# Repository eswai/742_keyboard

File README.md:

# 742 KEYBOARD

742はOLED搭載、54キーの分割キーボードです。
ファームウェアは [QMK](https://github.com/eswai/qmk_firmware/tree/master/keyboards/eswai/742) を参照ください。

本キーボードはMITライセンスです。

foostan氏のKiCADライブラリ[kbd](https://github.com/foostan/kbd)を使用させていただきました。

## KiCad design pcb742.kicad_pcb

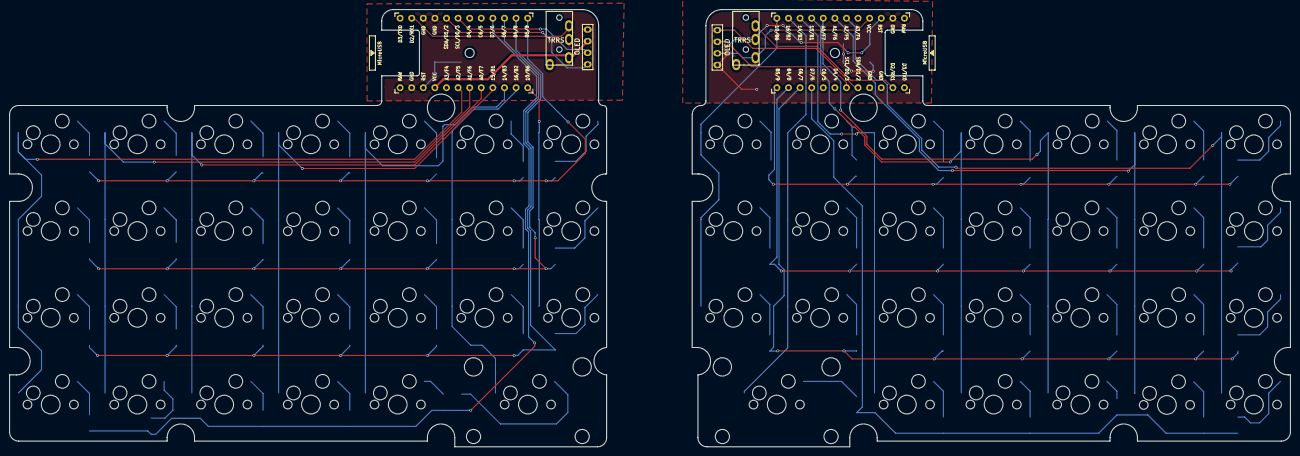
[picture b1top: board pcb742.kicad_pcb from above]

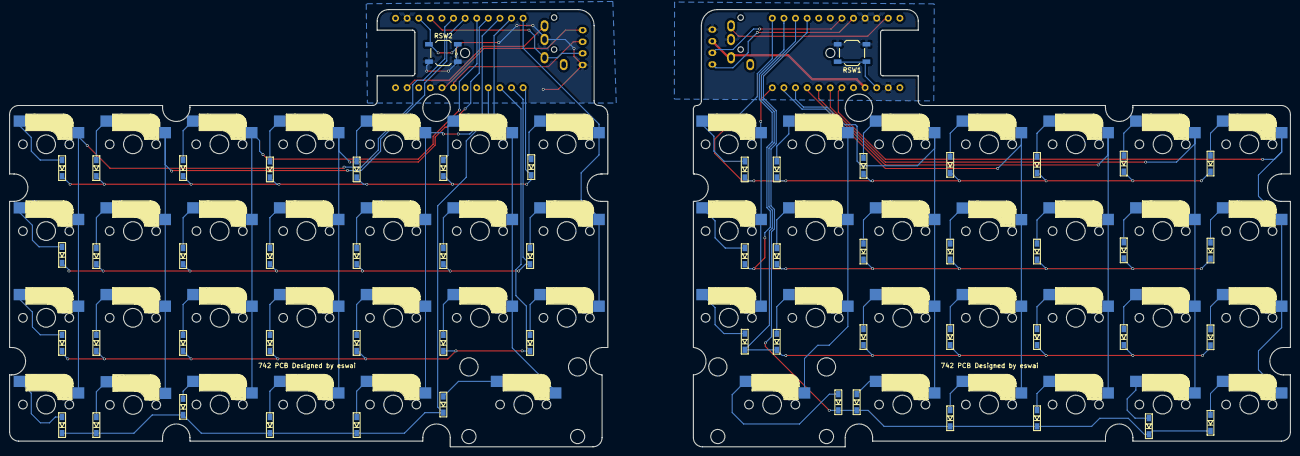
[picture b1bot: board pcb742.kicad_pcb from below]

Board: 2 copper layers, 280.5 x 95.8 mm, 116 parts (56 on the bottom side), 88 nets.

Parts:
D1, D2, D3, D4, D5, D6, D7, D8, D9, D10, D11, D12, D13, D14, D15, D16, D17, D18, D19, D20, D21, D22, D23, D24, D25, D26, D27, D28, D29, D30, D31, D32, D33, D34, D35, D36, D37, D38, D39, D40, D41, D42, D43, D44, D45, D46, D47, D48, D49, D50, D51, D52, D53, D54: D; D3_SMD_v2
J1, J3: MJ-4PP-9; MJ-4PP-9_1side
J2, J4: OLED; OLED_1side
RSW1, RSW2: SW_PUSH; SW_SPST_TL3342
SW1, SW2, SW3, SW4, SW5, SW6, SW7, SW8, SW9, SW10, SW11, SW12, SW13, SW14, SW15, SW16, SW17, SW18, SW19, SW20, SW21, SW22, SW23, SW24, SW25, SW26, SW27, SW28, SW29, SW30, SW31, SW32, SW33, SW34, SW35, SW36, SW37, SW38, SW39, SW40, SW41, SW42, SW43, SW44, SW45, SW46, SW47, SW48, SW49, SW50, SW51, SW52, SW53, SW54: SW_PUSH; CherryMX_Hotswap
U1, U2: ProMicro; ProMicro_v3

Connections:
GND: J1.C, J2.4, RSW1.2, U1.3, U1.4, U1.23
GNDA: J3.C, J4.4, RSW2.2, U2.3, U2.4, U2.23
unnamed: D1.2, SW1.2
unnamed: D2.2, SW2.2
unnamed: D3.2, SW3.2
unnamed: D4.2, SW4.2
unnamed: D5.2, SW5.2
unnamed: D6.2, SW6.2
unnamed: D7.2, SW7.2
unnamed: D8.2, SW8.2
unnamed: D9.2, SW9.2
unnamed: D10.2, SW10.2
unnamed: D11.2, SW11.2
unnamed: D12.2, SW12.2
unnamed: D13.2, SW13.2
unnamed: D14.2, SW14.2
unnamed: D15.2, SW15.2
unnamed: D16.2, SW16.2
unnamed: D17.2, SW17.2
unnamed: D18.2, SW18.2
unnamed: D19.2, SW19.2
unnamed: D20.2, SW20.2
unnamed: D21.2, SW21.2
unnamed: D22.2, SW22.2
unnamed: D23.2, SW23.2
unnamed: D24.2, SW24.2
unnamed: D25.2, SW25.2
unnamed: D26.2, SW26.2
unnamed: D27.2, SW27.2
unnamed: D28.2, SW28.2
unnamed: D29.2, SW29.2
unnamed: D30.2, SW30.2
unnamed: D31.2, SW31.2
unnamed: D32.2, SW32.2
unnamed: D33.2, SW33.2
unnamed: D34.2, SW34.2
unnamed: D35.2, SW35.2
unnamed: D36.2, SW36.2
unnamed: D37.2, SW37.2
unnamed: D38.2, SW38.2
unnamed: D39.2, SW39.2
unnamed: D40.2, SW40.2
unnamed: D41.2, SW41.2
unnamed: D42.2, SW42.2
unnamed: D43.2, SW43.2
unnamed: D44.2, SW44.2
unnamed: D45.2, SW45.2
unnamed: D46.2, SW46.2
unnamed: D47.2, SW47.2
unnamed: D48.2, SW48.2
unnamed: D49.2, SW49.2
unnamed: D50.2, SW50.2
unnamed: D51.2, SW51.2
unnamed: D52.2, SW52.2
unnamed: D53.2, SW53.2
unnamed: D54.2, SW54.2
SCL: J2.2, U1.6
SCL_r: J4.2, U2.6
SDA: J2.1, U1.5
SDA_r: J4.1, U2.5
VCC: J1.D, J2.3, U1.21
VDD: J3.D, J4.3, U2.21
col0: SW1.1, SW8.1, SW15.1, SW22.1, U1.19
col0_r: SW28.1, SW35.1, SW42.1, SW49.1, U2.19
col1: SW2.1, SW9.1, SW16.1, SW23.1, U1.18
col1_r: SW29.1, SW36.1, SW43.1, SW50.1, U2.18
col2: SW3.1, SW10.1, SW17.1, SW24.1, U1.17
col2_r: SW30.1, SW37.1, SW44.1, SW51.1, U2.17
col3: SW4.1, SW11.1, SW18.1, SW25.1, U1.16
col3_r: SW31.1, SW38.1, SW45.1, SW52.1, U2.16
col4: SW5.1, SW12.1, SW19.1, SW26.1, U1.15
col4_r: SW32.1, SW39.1, SW46.1, SW53.1, U2.15
col5: SW6.1, SW13.1, SW20.1, SW27.1, U1.14
col5_r: SW33.1, SW40.1, SW47.1, SW54.1, U2.14
col6: SW7.1, SW14.1, SW21.1, U1.13
col6_r: SW34.1, SW41.1, SW48.1, U2.13
data: J1.B, U1.2
data_r: J3.B, U2.2
reset: RSW1.1, U1.22
reset_r: RSW2.1, U2.22
row0: D1.1, D2.1, D3.1, D4.1, D5.1, D6.1, D7.1, U1.12
row0_r: D28.1, D29.1, D30.1, D31.1, D32.1, D33.1, D34.1, U2.12
row1: D8.1, D9.1, D10.1, D11.1, D12.1, D13.1, D14.1, U1.11
row1_r: D35.1, D36.1, D37.1, D38.1, D39.1, D40.1, D41.1, U2.11
row2: D15.1, D16.1, D17.1, D18.1, D19.1, D20.1, D21.1, U1.10
row2_r: D42.1, D43.1, D44.1, D45.1, D46.1, D47.1, D48.1, U2.10
row3: D22.1, D23.1, D24.1, D25.1, D26.1, D27.1, U1.9
row3_r: D49.1, D50.1, D51.1, D52.1, D53.1, D54.1, U2.9

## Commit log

2020-12-05 gitignore
2020-12-05 kbd library
2020-12-05 Case CAD model
